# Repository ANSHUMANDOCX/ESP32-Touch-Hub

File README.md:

# ESP32-S3 Smart Hub

## Description
This is a ESP32-S3 Based HUB paired with a touch screen that can be used for anything that one wants but for me i will be using it to connect all my ESP32 project and control it from one place and get a whole lot more connected experience between my project.

---
## Parts Used
- ESP32 S3 Used as the brains of the system
- CH340C for onboard programming. 
- 3.5" ILI9488 SPI touch display (MSP3520 module) for UI interaction
- Battery-powered with USB-C charging and intelligent load sharing
- Onboard SD card for storing web assets, UI resources, and sensor logs
- 3 tactile buttons + passive buzzer for physical interaction and alerts
- Charging status indicators both physical and UI based
---
## Technicals 
- The board will have dual volages 5V and 3.3v for the TFT and ESP32.
- It uses a load sharing circuit where when the battery is charging the board will be powered from the USB
- I will pair a 1800mah Lipo Battery so i can get a considerable amount of battery life.
- the board is using a MT3608 and ME6217C33M5G ics for 5v and 3.3v regulator along with a MCP73833 for charging the battery

## Firmware
THe code is tested just put your wifi and password and its ready to go 

## PCB SCHEMATIC and CAD 

## BUILD 
Demo Link https://youtube.com/shorts/PqJHbwtBgcA

## BOM
| Product Name | Quantity | Price ($) | Vendor |
|---|---:|---:|---|
| [ME6217C33M5G 3.3V LDO Regulator](https://sharvielectronics.com/product/me6217c33m5g-3-3v-800ma-fixed-ldo-voltage-regulator-sot-23-5-package/) | 1 | 0.30 | Sharvi Electronics |
| [ESP32-S3-WROOM-1 N16R8](https://sharvielectronics.com/product/esp32-s3-wroom-1-n16r8-16mb-flash-memory-wifi-and-bluetooth-module-41-smd-package/) | 1 | 4.51 | Sharvi Electronics |
| [FS8205A Dual N-Channel MOSFET](https://sharvielectronics.com/product/fs8205a-dual-n-channel-power-mosfet-lithium-battery-protection-tssop-8-package/) | 1 | 0.80 | Sharvi Electronics |
| [DW01A Battery Protection IC](https://sharvielectronics.com/product/dw01a-lithium-battery-protection-ic-sot23-6/) | 1 | 0.55 | Sharvi Electronics |
| [MT3608 Step-Up Converter IC](https://sharvielectronics.com/product/mt3608-high-efficiency-1-2mhz-2a-step-up-converter-sot23-6-package/) | 1 | 0.85 | Sharvi Electronics |
| [Micro SD Card Socket 9-Pin SMD](https://sharvielectronics.com/product/micro-sd-memory-card-socket-9pin-smd/) | 1 |0.60| Sharvi Electronics |
| [MCP73833 Li-Ion Charger IC](https://robu.in/product/mcp73833-ami-un-microchip-battery-charger-for-1-cell-of-li-ion-li-pol-battery-6v-input-4-2v-1a-charge-msop-10) | 1 | 1.93 | Robu.in |
| [AO3401 P-Channel MOSFET](https://robu.in/product/ao3401a-umwyoutai-semiconductor-co-ltd-30v-4-2a-50m%cf%8910v-1-4w-400mv-1-piece-p-channel-sot-23-mosfets-rohs) | 1 | 0.37 | Robu.in |
| [3.5" TFT Touchscreen Display](https://techiesms.com/product/3-5-inch-tft-touchscreen-display/) | 1 | 11.62 | Techiesms |
| Passives (Resistors, Capacitors, Pull-ups, etc.) | Assorted | 8 | Sharvi Electronics |
|PCB||2|ALLPCB|
|SHIPPING||1||
|Total||35||

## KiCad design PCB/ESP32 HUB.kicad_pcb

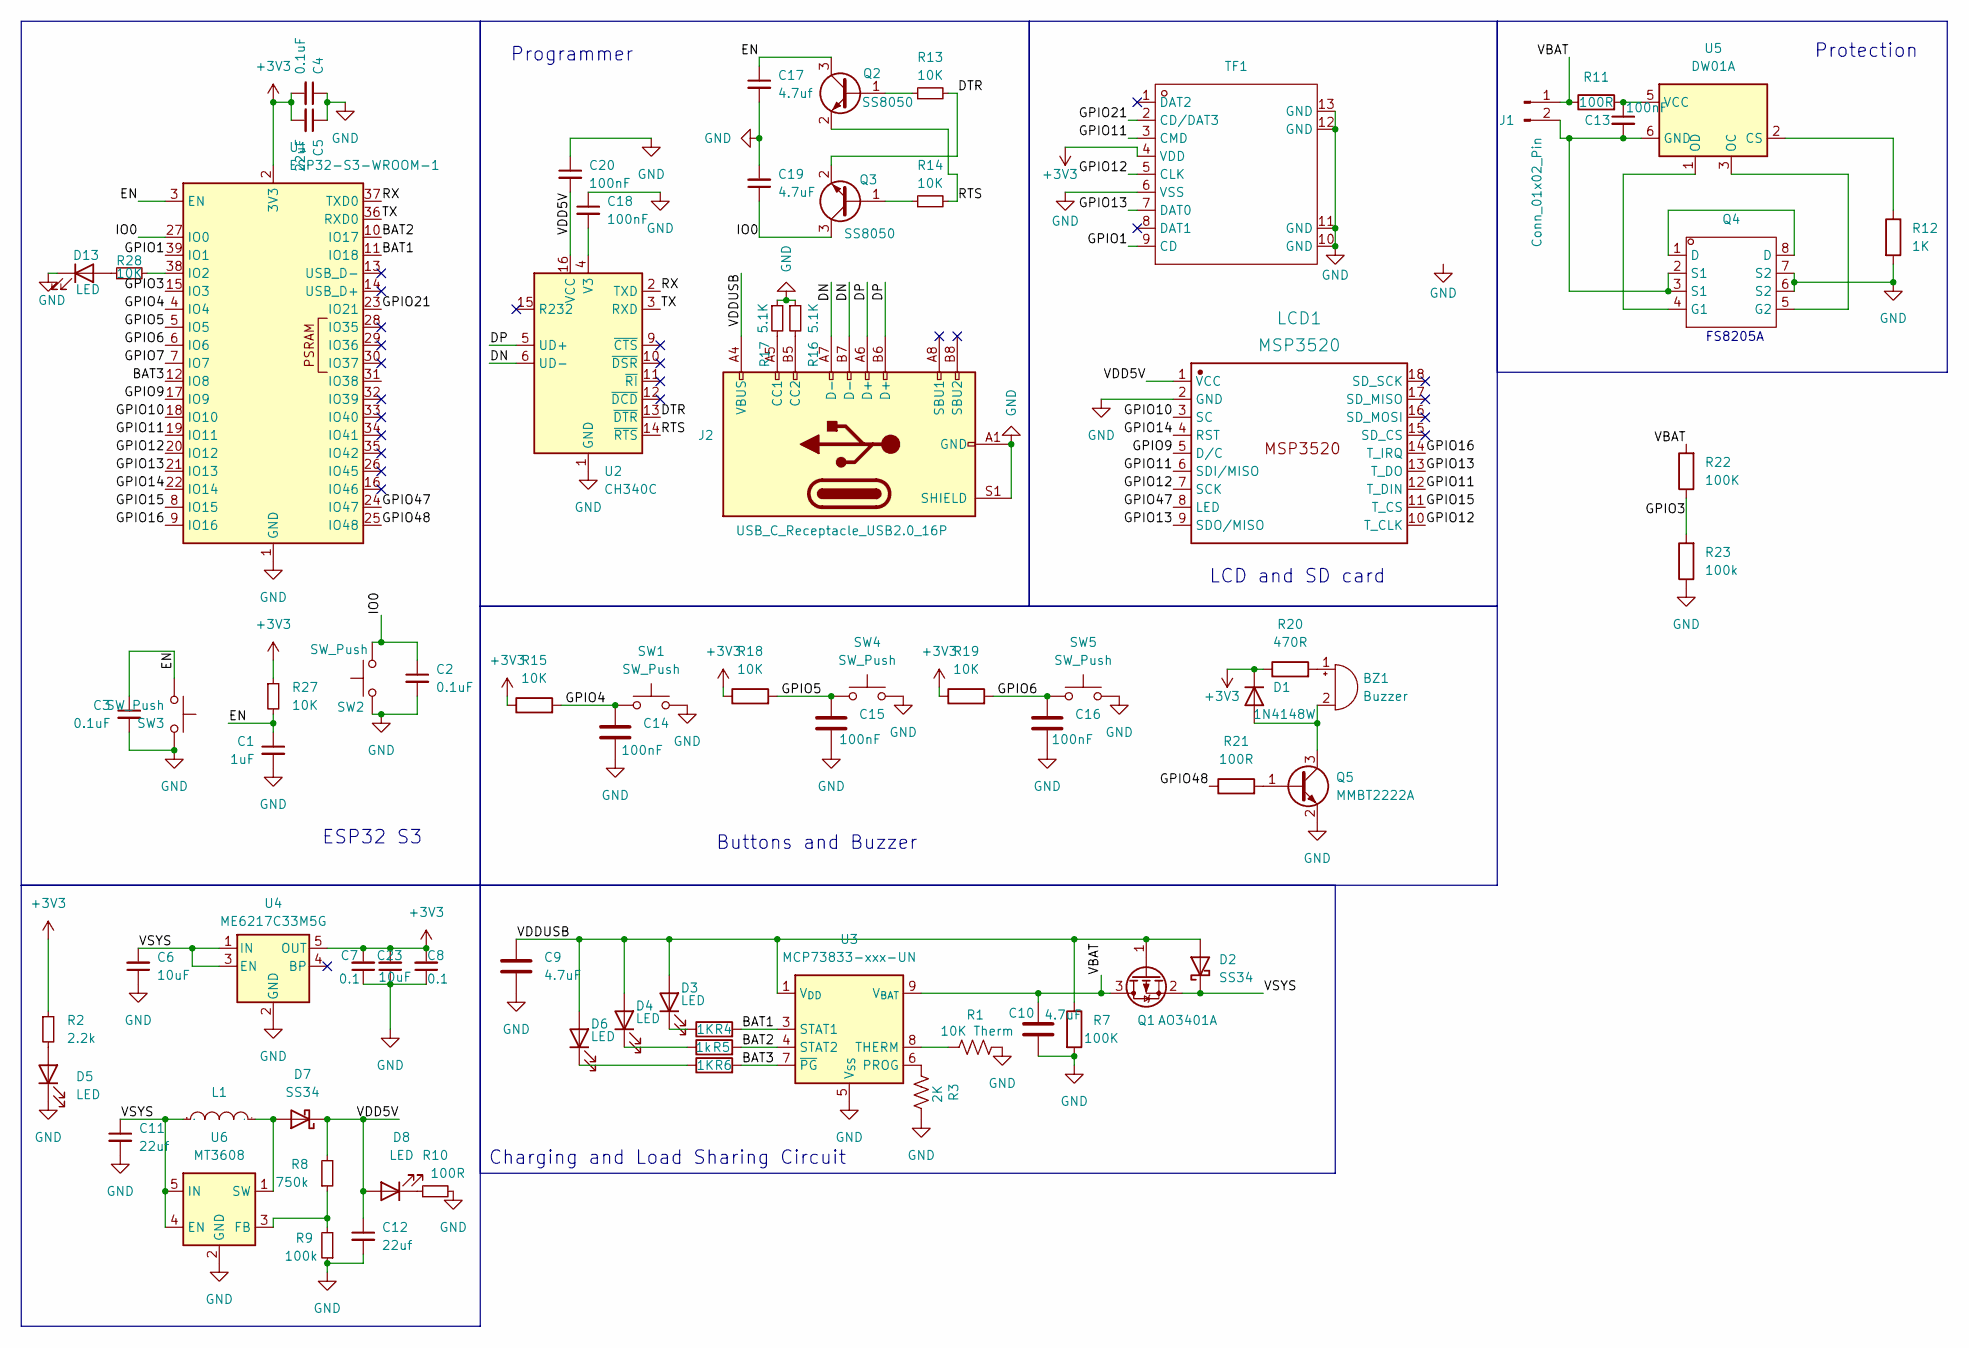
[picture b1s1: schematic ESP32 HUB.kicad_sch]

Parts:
BZ1: Buzzer; Buzzer_12x9.5RM7.6
C1: 1uF; C_0603_1608Metric
C2, C3, C4: 0.1uF; C_0603_1608Metric
C5: 22uF; C_0603_1608Metric
C6, C23: 10uF; C_0603_1608Metric_Pad1.08x0.95mm_HandSolder
C7, C8: 0.1; C_0603_1608Metric_Pad1.08x0.95mm_HandSolder
C9, C10: 4.7uF; C_0603_1608Metric
C11, C12: 22uf; C_0603_1608Metric
C13, C14, C15, C16: 100nF; C_0603_1608Metric
C17: 4.7uf; C_0603_1608Metric_Pad1.08x0.95mm_HandSolder
C18, C20: 100nF; C_0603_1608Metric_Pad1.08x0.95mm_HandSolder
C19: 4.7uF; C_0603_1608Metric_Pad1.08x0.95mm_HandSolder
D1: 1N4148W; D_SOD-123
D2, D7: SS34; D_SMA
D3, D4, D5, D6, D8, D13: LED; LED_0603_1608Metric
J1: Conn_01x02_Pin; JST_XH_B2B-XH-AM_1x02_P2.50mm_Vertical
J2: USB_C_Receptacle_USB2.0_16P; USB_C_Receptacle_GCT_USB4105-xx-A_16P_TopMnt_Horizontal
L1: 22uH; IND-SMD_L4.0-W4.0; Manufacturer Part ANR4030T220M; LCSC Part Name 22uH ±20% 1.4A 4x4x3mm
LCD1: MSP3520; Manufacturer Part MSP3520
Q1: AO3401A; SOT-23
Q2, Q3: SS8050; SOT-23
Q4: TSSOP-8_L4.4-W3.0-P0.65-LS6.4-BL-2; Manufacturer Part FS8205A; LCSC Part Name 2个N沟道 耐压:20V 电流:6A
Q5: MMBT2222A; SOT-23
R1: 10K Therm; R_0603_1608Metric_Pad0.98x0.95mm_HandSolder
R2: 2.2k; R_0603_1608Metric_Pad0.98x0.95mm_HandSolder
R3: 2K; R_0603_1608Metric_Pad0.98x0.95mm_HandSolder
R4, R6, R12: 1K; R_0603_1608Metric_Pad0.98x0.95mm_HandSolder
R5: 1k; R_0603_1608Metric_Pad0.98x0.95mm_HandSolder
R7, R22: 100K; R_0603_1608Metric_Pad0.98x0.95mm_HandSolder
R8: 750k; R_0603_1608Metric_Pad0.98x0.95mm_HandSolder
R9, R23: 100k; R_0603_1608Metric_Pad0.98x0.95mm_HandSolder
R10, R11, R21: 100R; R_0603_1608Metric_Pad0.98x0.95mm_HandSolder
R13, R14, R15, R18, R19, R27, R28: 10K; R_0603_1608Metric_Pad0.98x0.95mm_HandSolder
R16, R17: 5.1K; R_0603_1608Metric_Pad0.98x0.95mm_HandSolder
R20: 470R; R_0603_1608Metric_Pad0.98x0.95mm_HandSolder
SW1, SW4, SW5: SW_Push; SW_TH_Tactile_Omron_B3F-100x
SW2, SW3: SW_Push; SW_Push_SPST_NO_Alps_SKRK
TF1: TF-SMD_TF-CARD-H1.8; Manufacturer Part TF-CARD H1.8; LCSC Part Name 9P，自弹式TF卡座
U1: ESP32-S3-WROOM-1
U2: CH340C; SOIC-16_3.9x9.9mm_P1.27mm
U3: MCP73833-xxx-UN; MSOP-10_3x3mm_P0.5mm
U4: ME6217C33M5G; SOT-23-5
U5: DW01A; SOT-23-6
U6: MT3608; SOT-23-6

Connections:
+3V3: C4.2, C5.2, C7.2, C8.2, C23.2, D1.1 (K), R2.1, R15.1, R18.1, R19.1, R20.1, R27.1, TF1.4 (VDD), U1.2 (3V3), U4.5 (OUT)
/BAT1: R4.2, U1.11 (IO18), U3.3 (STAT1)
/BAT2: R5.2, U1.10 (IO17), U3.4 (STAT2)
/BAT3: R6.2, U1.12 (IO8), U3.7 (~PG)
/DN: J2.A7 (D-), J2.B7 (D-), U2.6 (UD-)
/DP: J2.A6 (D+), J2.B6 (D+), U2.5 (UD+)
/DTR: Q3.2 (E), R13.2, U2.13 (~DTR)
/EN: C1.1, C3.1, C17.1, Q2.3 (C), R27.2, SW3.1, U1.3 (EN)
/GPIO1: TF1.9 (CD), U1.39 (IO1)
/GPIO3: R22.1, R23.2, U1.15 (IO3)
/GPIO4: C14.1, R15.2, SW1.1, U1.4 (IO4)
/GPIO5: C15.1, R18.2, SW4.1, U1.5 (IO5)
/GPIO6: C16.1, R19.2, SW5.1, U1.6 (IO6)
/GPIO7: U1.7 (IO7)
/GPIO9: LCD1.5 (D/C), U1.17 (IO9)
/GPIO10: LCD1.3 (SC), U1.18 (IO10)
/GPIO11: LCD1.6 (SDI/MISO), LCD1.12 (T_DIN), TF1.3 (CMD), U1.19 (IO11)
/GPIO12: LCD1.7 (SCK), LCD1.10 (T_CLK), TF1.5 (CLK), U1.20 (IO12)
/GPIO13: LCD1.9 (SDO/MISO), LCD1.13 (T_DO), TF1.7 (DAT0), U1.21 (IO13)
/GPIO14: LCD1.4 (RST), U1.22 (IO14)
/GPIO15: LCD1.11 (T_CS), U1.8 (IO15)
/GPIO16: LCD1.14 (T_IRQ), U1.9 (IO16)
/GPIO21: TF1.2 (CD/DAT3), U1.23 (IO21)
/GPIO47: LCD1.8 (LED), U1.24 (IO47)
/GPIO48: R21.1, U1.25 (IO48)
/IO0: C2.1, C19.1, Q3.3 (C), SW2.1, U1.27 (IO0)
/RTS: Q2.2 (E), R14.2, U2.14 (~RTS)
/RX: U1.37 (TXD0), U2.2 (TXD)
/TX: U1.36 (RXD0), U2.3 (RXD)
/VBAT: C10.1, J1.1, Q1.3 (D), R11.1, R22.2, U3.9 (V_{BAT}), U3.10 (V_{BAT})
/VDD5V: C12.1, C20.2, D7.1 (K), D8.2 (A), LCD1.1 (VCC), R8.2, U2.16 (VCC)
/VDDUSB: C9.1, D2.2 (A), D3.2 (A), D4.2 (A), D6.2 (A), J2.A4 (VBUS), J2.A9 (VBUS), J2.B4 (VBUS), J2.B9 (VBUS), Q1.1 (G), R7.1, U3.1 (V_{DD}), U3.2 (V_{DD})
/VSYS: C6.2, C11.1, D2.1 (K), L1.1, Q1.2 (S), U4.1 (IN), U4.3 (EN), U6.4 (EN), U6.5 (IN)
GND: C1.2, C2.2, C3.2, C4.1, C5.1, C6.1, C7.1, C8.1, C9.2, C10.2, C11.2, C12.2, C14.2, C15.2, C16.2, C17.2, C18.1, C19.2, C20.1, C23.1, D5.1 (K), D13.1 (K), J2.A1 (GND), J2.A12 (GND), J2.B1 (GND), J2.B12 (GND), J2.S1 (SHIELD), LCD1.2 (GND), Q4.6 (S2), Q4.7 (S2), Q5.2 (E), R1.2, R3.2, R7.2, R9.1, R10.2, R12.2, R16.1, R17.1, R23.1, SW1.2, SW2.2, SW3.2, SW4.2, SW5.2, TF1.6 (VSS), TF1.10 (GND), TF1.11 (GND), TF1.12 (GND), TF1.13 (GND), U1.1 (GND), U1.40 (GND), U1.41 (GND), U2.1 (GND), U3.5 (V_{SS}), U4.2 (GND), U6.2 (GND)
unnamed: BZ1.1 (+), R20.2
unnamed: BZ1.2 (-), D1.2 (A), Q5.3 (C)
unnamed: D3.1 (K), R4.1
unnamed: D4.1 (K), R5.1
unnamed: D5.2 (A), R2.2
unnamed: D6.1 (K), R6.1
unnamed: D7.2 (A), L1.2, U6.1 (SW)
unnamed: D8.1 (K), R10.1
unnamed: D13.2 (A), R28.1
unnamed: C13.2, J1.2, Q4.2 (S1), Q4.3 (S1), U5.6 (GND)
unnamed: J2.A5 (CC1), R17.2
unnamed: J2.B5 (CC2), R16.2
unnamed: Q2.1 (B), R13.1
unnamed: Q3.1 (B), R14.1
unnamed: Q4.1 (D), Q4.8 (D)
unnamed: Q4.4 (G1), U5.1 (OD)
unnamed: Q4.5 (G2), U5.3 (OC)
unnamed: Q5.1 (B), R21.2
unnamed: R28.2, U1.38 (IO2)
unnamed: C18.2, U2.4 (V3)
unnamed: R3.1, U3.6 (PROG)
unnamed: R1.1, U3.8 (THERM)
unnamed: R12.1, U5.2 (CS)
unnamed: C13.1, R11.2, U5.5 (VCC)
unnamed: R8.1, R9.2, U6.3 (FB)

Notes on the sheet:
FS8205A
Buttons and Buzzer
Programmer
Charging and Load Sharing Circuit
LCD and SD card
Protection
ESP32 S3

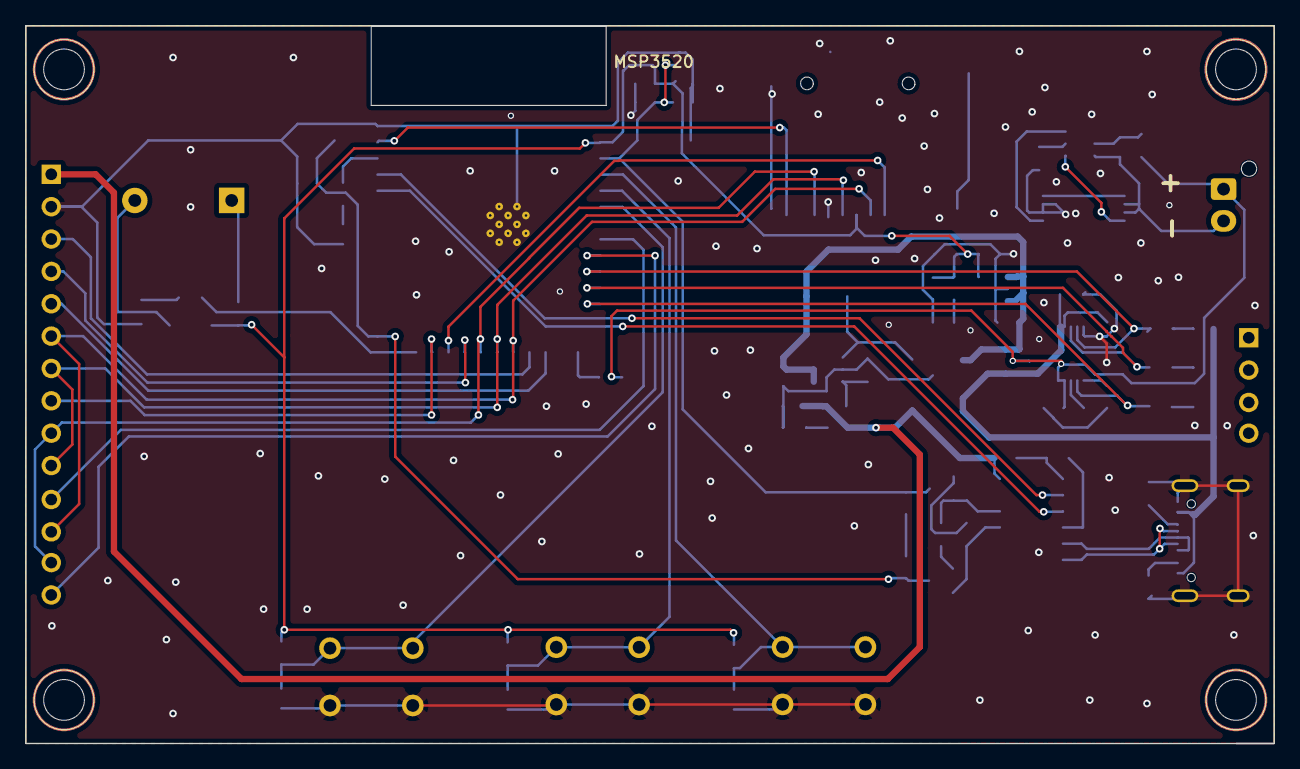
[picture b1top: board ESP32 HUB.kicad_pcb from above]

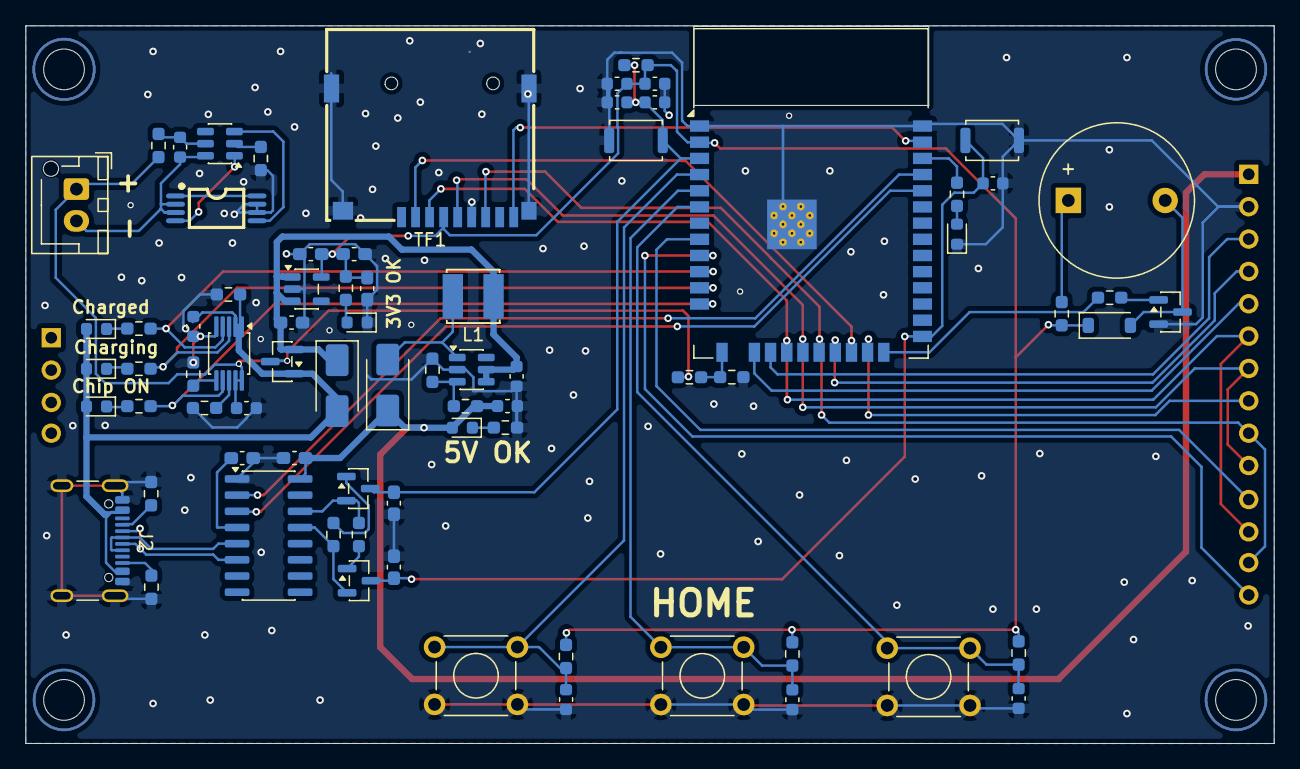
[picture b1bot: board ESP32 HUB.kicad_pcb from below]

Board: 2 copper layers, 98.0 x 56.3 mm, 77 parts (76 on the bottom side), 58 nets.

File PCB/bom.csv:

Designator,Footprint,Quantity,Value,LCSC Part #
BZ1,Buzzer_12x9.5RM7.6,1,Buzzer,
C1,0603,1,1uF,
"C10, C17, C19, C9",0603,4,4.7uF,
"C11, C12, C5",0603,3,22uf,
"C13, C14, C15, C16, C18, C20",0603,6,100nF,
"C2, C3, C4",0603,3,0.1uF,
"C23, C6",0603,2,10uF,
"C7, C8",0603,2,0.1,
D1,D_SOD-123,1,1N4148W,
"D13, D3, D4, D5, D6, D8",0603,6,LED,
"D2, D7",D_SMA,2,SS34,
J1,JST_XH_B2B-XH-AM_1x02_P2.50mm_Vertical,1,Conn_01x02_Pin,
J2,USB_C_Receptacle_GCT_USB4105-xx-A_16P_TopMnt_Horizontal,1,USB_C_Receptacle_USB2.0_16P,
L1,IND-SMD_L4.0-W4.0,1,22uH,
LCD1,MSP3520,1,MSP3520,
Q1,SOT-23,1,AO3401A,
"Q2, Q3",SOT-23,2,SS8050,
Q4,TSSOP-8_L4.4-W3.0-P0.65-LS6.4-BL-2,1,~,
Q5,SOT-23,1,MMBT2222A,
R1,0603,1,10K Therm,
"R10, R11, R21",0603,3,100R,
"R12, R4, R5, R6",0603,4,1K,
"R13, R14, R15, R18, R19, R27, R28",0603,7,10K,
"R16, R17",0603,2,5.1K,
R2,0603,1,2.2k,
R20,0603,1,470R,
"R22, R23, R7, R9",0603,4,100K,
R3,0603,1,2K,
R8,0603,1,750k,
"SW1, SW4, SW5",SW_TH_Tactile_Omron_B3F-100x,3,SW_Push,
"SW2, SW3",SW_Push_SPST_NO_Alps_SKRK,2,SW_Push,
TF1,TF-SMD_TF-CARD-H1.8,1,~,
U1,ESP32-S3-WROOM-1,1,ESP32-S3-WROOM-1,
U2,SOIC-16_3.9x9.9mm_P1.27mm,1,CH340C,
U3,MSOP-10_3x3mm_P0.5mm,1,MCP73833-xxx-UN,
U4,SOT-23-5,1,ME6217C33M5G,
U5,SOT-23-6,1,DW01A,
U6,SOT-23-6,1,MT3608,

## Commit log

2026-06-14 Add demo link to README
    Added a demo link to the BUILD section.
